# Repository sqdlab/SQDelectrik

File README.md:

# SQDelectrik

This repository details custom electronic circuits for general lab use. This repository holds the schematics and usage documentation:

- [Safe Ohmmeter](Projects/SafeOhmmeter/README.md)
- [Safe Ohmmeter v2](Projects/SafeOhmmeter2/README.md)

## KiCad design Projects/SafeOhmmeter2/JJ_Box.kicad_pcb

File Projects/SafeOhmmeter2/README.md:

# Safe Ohmmeter v2

Multimeters can measure resistance, but may set a large voltage across the device under test. Inspired by a [project in Delft](https://qtwork.tudelft.nl/~schouten/oldstuff/viboxjunction-p.htm), this is a modernised circuit that:

- Sets a fixed $10\textnormal{mV}$ across the sample
- Maps the resulting resistance into a voltage that is inversely proportional to the measured resistance
- This voltage can be read using a conventional multimeter set to voltage measurement mode

That is, this is a simple device aids in measuring resistance while keeping a safe voltage across the device under test.

## General usage

The device runs off 3 AA batteries:

The operation is as follows:

- The left dial turns on the device. When moving it midway between OFF and ON, it will light the LED to show that the battery is functional
- The toggle switch switches the polarity of the probe voltage across the device under test (measured from centre-pin to the ground-shield of the isolated BNC connector)
- The device under test is connected into the BNC connector labelled INPUT
- The resistance of the device under test is mapped onto a voltage from 1mV to 5V given by the range set by the right dial (selecting over: $1/R$, $100/R$ and $10000/R$). Measure this voltage via a multimeter connected to the OUTPUT BNC connector

There is a handy table that helps with the conversion between measured voltage and the sample resistance.

## Recalibrating the gains

The inputs should measure $\pm10\textnormal{mV}$. If not, then open the box and tune the VREF trimpot. Note that if it does not breach $10\textnormal{mV}$, check the batteries.

To recalibrate open the box and connect a resistor across the input and measure the voltage as follows:

- To tune the $1/R$ range, connect a $10\Omega$ resistor across the input and turn the $1/R$ trimpot so that the output reads exactly $0.1\textnormal{V}$.
- To tune the $100/R$ range, connect a $1\textnormal{k}\Omega$ resistor across the input and turn the $100/R$ trimpot so that the output reads exactly $0.1\textnormal{V}$.
- To tune the $10000/R$ range, connect a $100\textnormal{k}\Omega$ resistor across the input and turn the $10000/R$ trimpot so that the output reads exactly $0.1\textnormal{V}$.

The three trimpots on the PCB corresponding to the three ranges are:

## Method of operation

View the full schematic [here](Docs/Schematic.pdf). The device is a simple OPAMP amplifier:

- The OPAMP is fed a constant DC $10\textnormal{mV}$ on its $+$ input
- Since it is in negative feedback mode, the voltage on the $-$ input is also $10\textnormal{mV}$
- KCL at the $-$ input for a sample resistance $R_s$ and feedback resistance $R_f$ gives $V_-/R_S+(V_--V_{out})/R_f=0$
- This simplifies into: $V_{out}=R_f/R_sV_-+V_-$. Since the output is measured with respect to $V_+=V_-$, the stray $V_-$ disappears to give $V_{meas}=0.01R_f/R_s$
- The three ranges thus, take $R_f=100\Omega$, $R_f=10\textnormal{k}\Omega$ and $R_f=1\textnormal{M}\Omega$.

There are additional diodes to clamp the voltage as a protective measure. The voltage reference is also tuned to give $10\textnormal{mV}$ (although it can be compensated with the feedback trimpots as well).

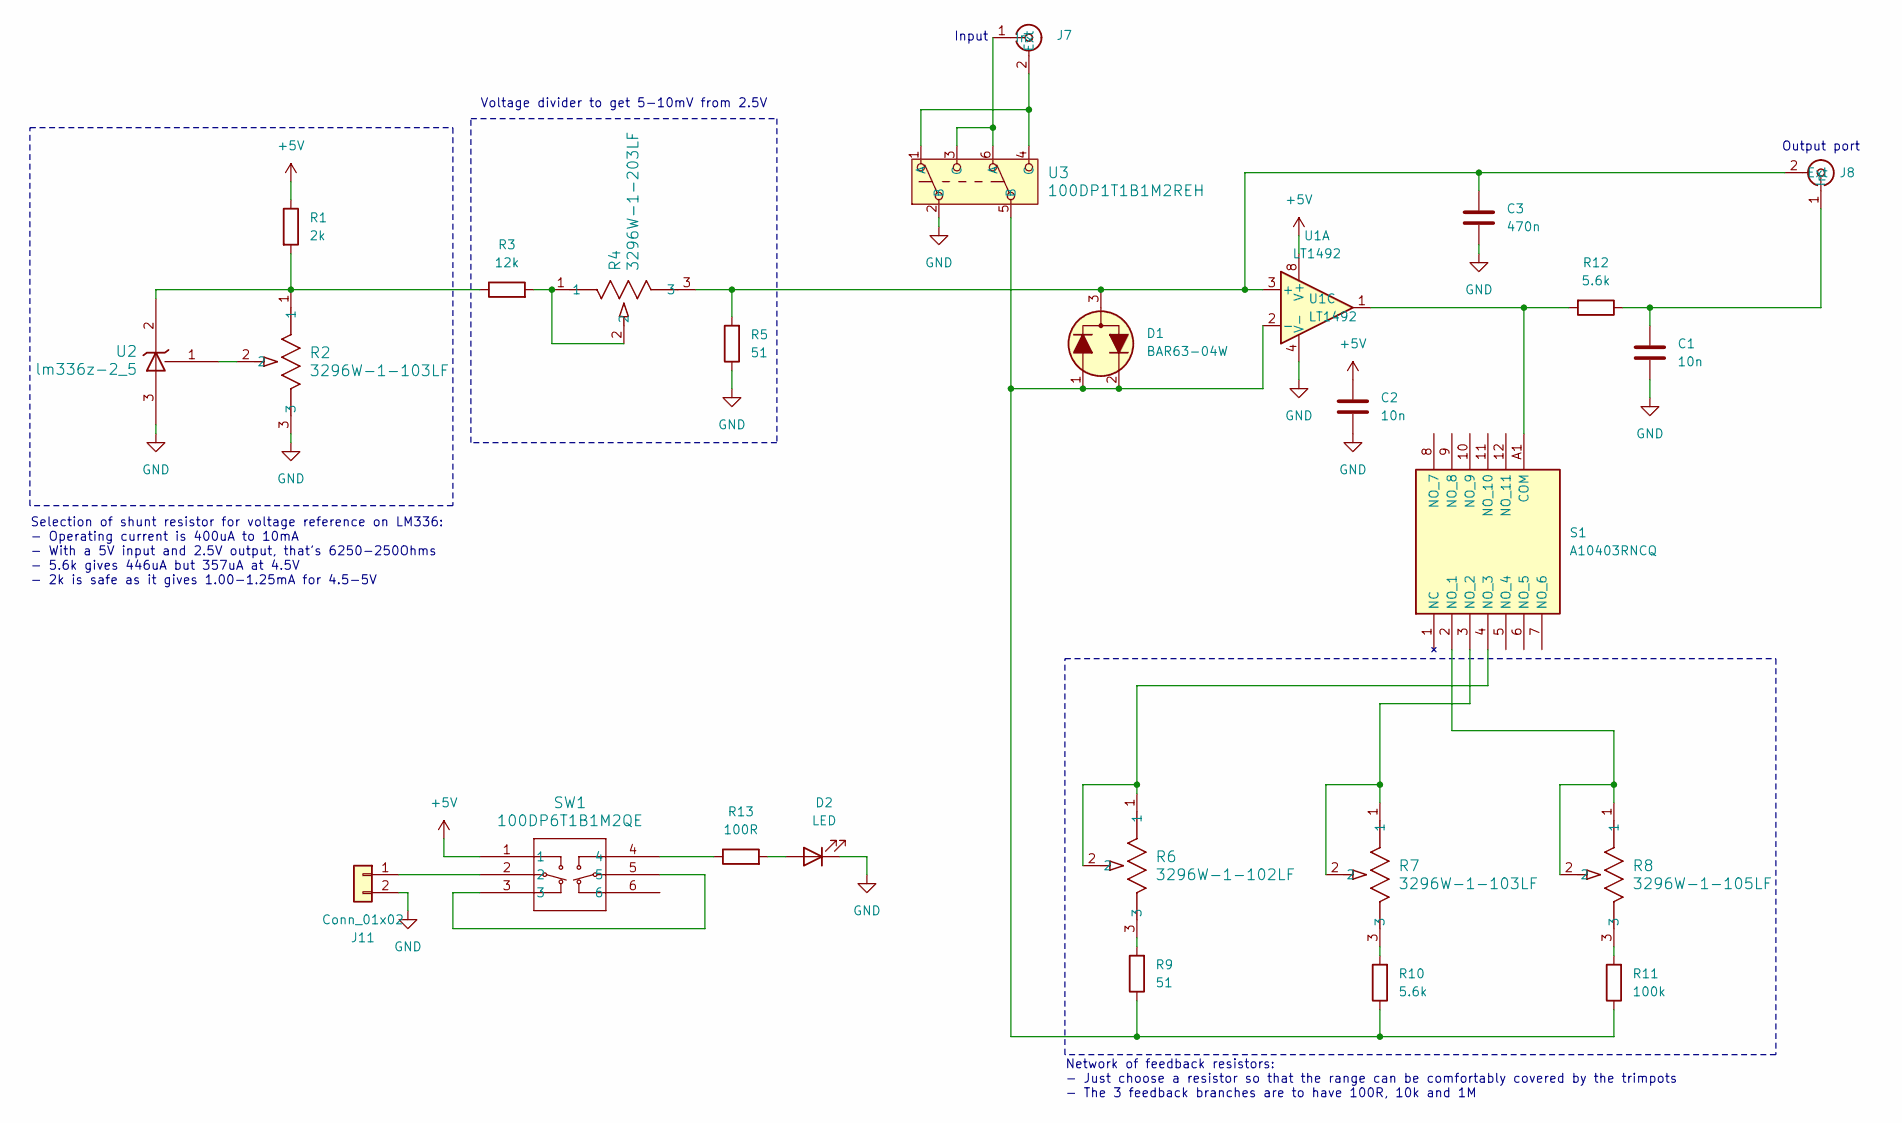
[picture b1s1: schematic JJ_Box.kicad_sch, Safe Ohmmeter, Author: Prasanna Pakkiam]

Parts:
C1, C2: 10n; C_0603_1608Metric_Pad1.08x0.95mm_HandSolder
C3: 470n; C_0603_1608Metric_Pad1.08x0.95mm_HandSolder
D1: BAR63-04W; SOT-323_SC-70_Handsoldering
D2: LED; LED_D5.0mm
J7, J8: CONN_5227222-3_TYC
J11: Conn_01x02; PinHeader_1x02_P2.54mm_Vertical
R1: 2k; R_0603_1608Metric_Pad0.98x0.95mm_HandSolder
R2, R7: 3296W-1-103LF; POT_3296W
R3: 12k; R_0603_1608Metric_Pad0.98x0.95mm_HandSolder
R4: 3296W-1-203LF; POT_3296W
R5, R9: 51; R_0603_1608Metric_Pad0.98x0.95mm_HandSolder
R6: 3296W-1-102LF; POT_3296W
R8: 3296W-1-105LF; POT_3296W
R10, R12: 5.6k; R_0603_1608Metric_Pad0.98x0.95mm_HandSolder
R11: 100k; R_0603_1608Metric_Pad0.98x0.95mm_HandSolder
R13: 100R; R_0603_1608Metric_Pad0.98x0.95mm_HandSolder
S1: A10403RNCQ; A10405RNCQE; Manufacturer_Part_Number A10403RNCQ
SW1: 100DP6T1B1M2QE; 100DP8T6B11M2QEH_EWI
U1: LT1492; SOIC-8_3.9x4.9mm_P1.27mm
U2: lm336z-2_5; Z03A_TEX
U3: 100DP1T1B1M2REH; SW6_100DP1T1B1M2REH

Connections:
+5V: C2.1, R1.1, SW1.1, U1.8 (V+)
GND: C1.2, C2.2, C3.2, D2.1 (K), J11.2, R2.3, R5.1, U1.4 (V-), U2.3 (-V), U3.2 (B)
unnamed: D1.1 (A), D1.2 (K), R9.1, R10.1, R11.1, U1.2 (-), U3.5 (B)
unnamed: C3.1, D1.3 (C), J8.2 (Ext), R4.3, R5.2, U1.3 (+)
unnamed: D2.2 (A), R13.2
unnamed: J7.2 (Ext), U3.1 (A), U3.4 (C)
unnamed: J7.1 (In), U3.3 (C), U3.6 (A)
unnamed: C1.1, J8.1 (In), R12.1
unnamed: J11.1, SW1.2
unnamed: R3.2, R4.1, R4.2
unnamed: R6.3, R9.2
unnamed: R7.3, R10.2
unnamed: R8.3, R11.2
unnamed: R13.1, SW1.4
unnamed: R12.2, S1.A1 (COM), U1.1
unnamed: R8.1, R8.2, S1.2 (NO_1)
unnamed: R7.1, R7.2, S1.3 (NO_2)
unnamed: R6.1, R6.2, S1.4 (NO_3)
unnamed: SW1.3, SW1.5
unnamed: R1.2, R2.1, R3.1, U2.2 (+V)
unnamed: R2.2, U2.1 (ADJ)

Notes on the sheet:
Voltage divider to get 5-10mV from 2.5V
Output port
Input
Network of feedback resistors: - Just choose a resistor so that the range can be comfortably covered by the trimpots - The 3 feedback branches are to have 100R, 10k and 1M
Selection of shunt resistor for voltage reference on LM336: - Operating current is 400uA to 10mA - With a 5V input and 2.5V output, that's 6250-250Ohms - 5.6k gives 446uA but 357uA at 4.5V - 2k is safe as it gives 1.00-1.25mA for 4.5-5V

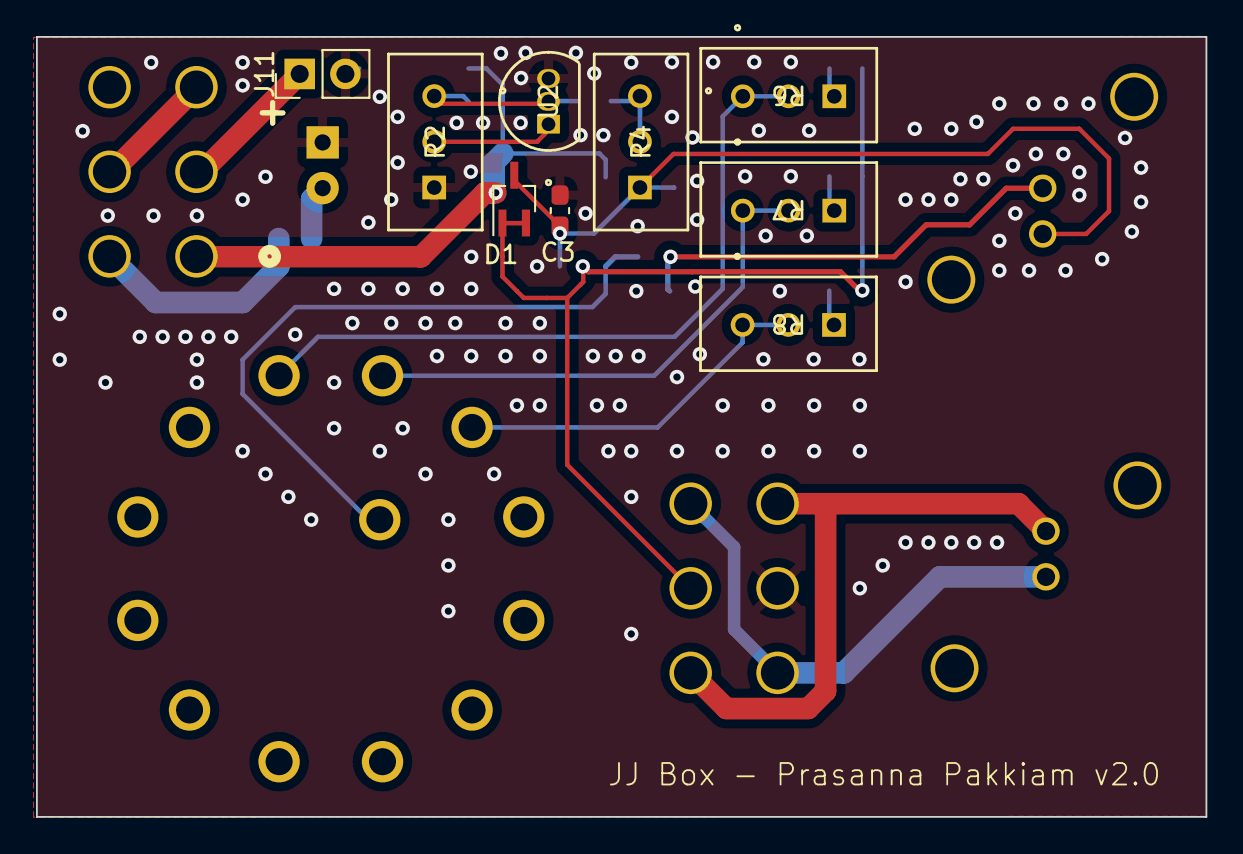
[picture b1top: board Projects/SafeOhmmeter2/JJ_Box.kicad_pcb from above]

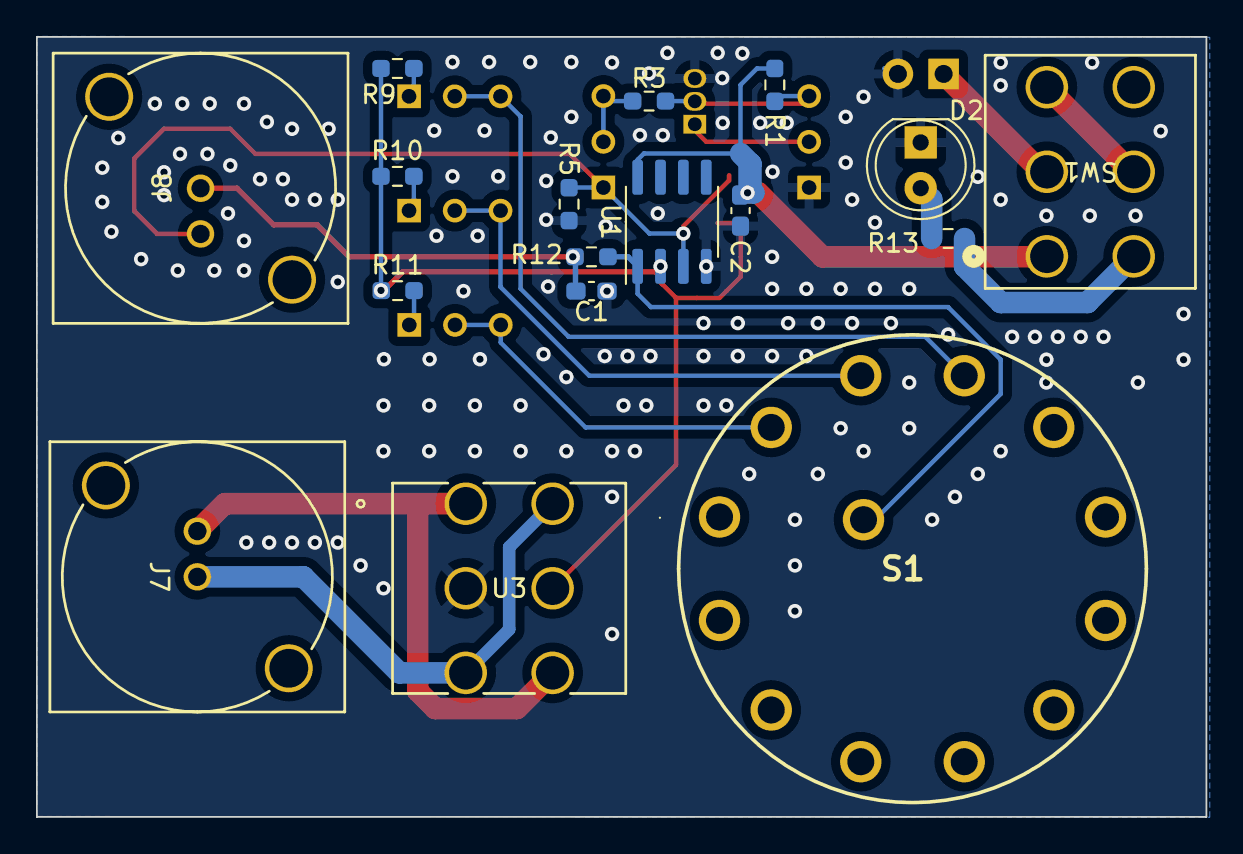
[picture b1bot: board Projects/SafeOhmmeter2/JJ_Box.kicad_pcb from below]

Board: 2 copper layers, 65.0 x 43.3 mm, 26 parts (17 on the bottom side), 21 nets.

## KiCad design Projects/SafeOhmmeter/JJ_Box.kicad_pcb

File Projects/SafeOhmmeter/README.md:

# Safe Ohmmeter

Multimeters can measure resistance, but may set a large voltage across the device under test. Inspired by a [project in Delft](https://qtwork.tudelft.nl/~schouten/oldstuff/viboxjunction-p.htm), this is a modernised circuit that:

- Sets a fixed $10\textnormal{mV}$ across the sample
- Maps the resulting resistance into a voltage that is inversely proportional to the measured resistance
- This voltage can be read using a conventional multimeter set to voltage measurement mode

That is, this is a simple device aids in measuring resistance while keeping a safe voltage across the device under test.

## General usage

The device runs off 3 AAA batteries:

The operation is as follows:

- The left dial turns on the device. When moving it midway between OFF and ON, it will light the LED to show that the battery is functional
- The toggle switch switches the polarity of the probe voltage across the device under test (measured from centre-pin to the ground-shield of the isolated BNC connector)
- The device under test is connected into the BNC connector labelled INPUT
- The resistance of the device under test is mapped onto a voltage from 1mV to 5V given by the range set by the right dial (selecting over: $1/R$, $100/R$ and $10000/R$). Measure this voltage via a multimeter connected to the OUTPUT BNC connector

There is a handy table that helps with the conversion between measured voltage and the sample resistance.

## Recalibrating the gains

To recalibrate open the box and connect a resistor across the input and measure the voltage as follows:

- To tune the $1/R$ range, connect a $10\Omega$ resistor across the input and turn the $1/R$ trimpot so that the output reads exactly $0.1\textnormal{V}$.
- To tune the $100/R$ range, connect a $1\textnormal{k}\Omega$ resistor across the input and turn the $100/R$ trimpot so that the output reads exactly $0.1\textnormal{V}$.
- To tune the $10000/R$ range, connect a $100\textnormal{k}\Omega$ resistor across the input and turn the $10000/R$ trimpot so that the output reads exactly $0.1\textnormal{V}$.

The three trimpots on the PCB corresponding to the three ranges are:

## Method of operation

View the full schematic [here](Docs/Schematic.pdf). The device is a simple OPAMP amplifier:

- The OPAMP is fed a constant DC $10\textnormal{mV}$ on its $+$ input
- Since it is in negative feedback mode, the voltage on the $-$ input is also $10\textnormal{mV}$
- KCL at the $-$ input for a sample resistance $R_s$ and feedback resistance $R_f$ gives $V_-/R_S+(V_--V_{out})/R_f=0$
- This simplifies into: $V_{out}=R_f/R_sV_-+V_-$. Since the output is measured with respect to $V_+=V_-$, the stray $V_-$ disappears to give $V_{meas}=0.01R_f/R_s$
- The three ranges thus, take $R_f=100\Omega$, $R_f=10\textnormal{k}\Omega$ and $R_f=1\textnormal{M}\Omega$.

There are additional diodes to clamp the voltage as a protective measure. The voltage reference is also tuned to give $10\textnormal{mV}$ (although it can be compensated with the feedback trimpots as well).

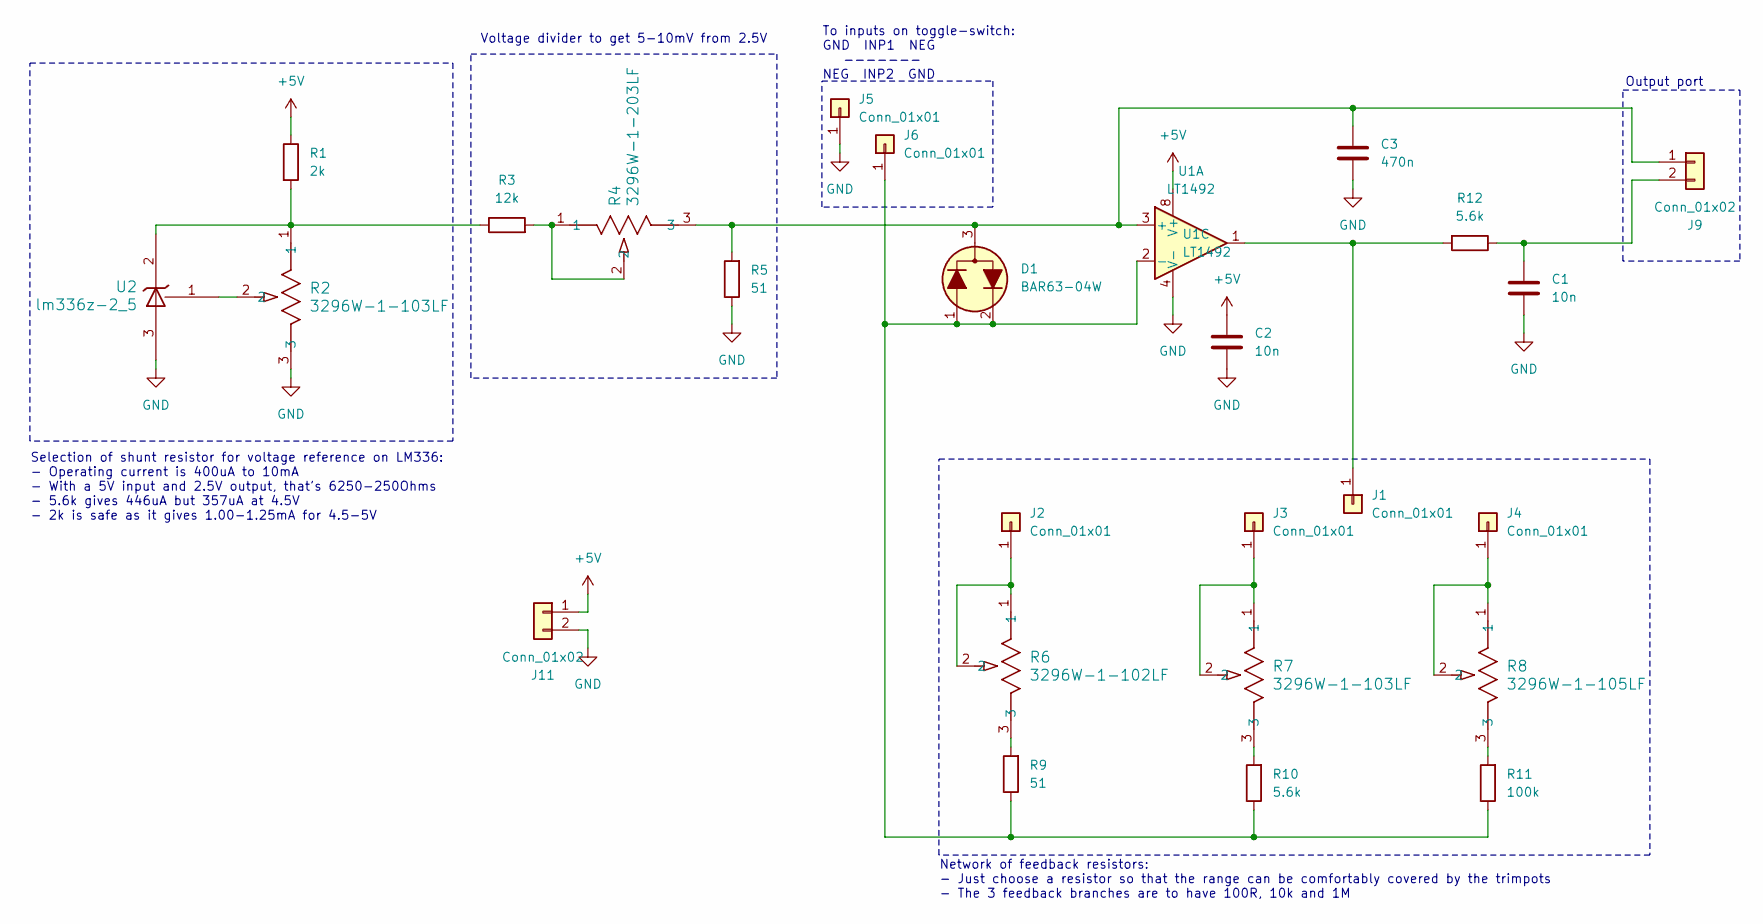
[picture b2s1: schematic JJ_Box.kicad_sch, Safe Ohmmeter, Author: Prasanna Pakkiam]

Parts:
C1, C2: 10n; C_0603_1608Metric_Pad1.08x0.95mm_HandSolder
C3: 470n; C_0603_1608Metric_Pad1.08x0.95mm_HandSolder
D1: BAR63-04W; SOT-323_SC-70_Handsoldering
J1, J2, J3, J4, J5, J6: Conn_01x01; PinHeader_1x01_P2.54mm_Vertical
J9, J11: Conn_01x02; PinHeader_1x02_P2.54mm_Vertical
R1: 2k; R_0603_1608Metric_Pad0.98x0.95mm_HandSolder
R2, R7: 3296W-1-103LF; POT_3296W
R3: 12k; R_0603_1608Metric_Pad0.98x0.95mm_HandSolder
R4: 3296W-1-203LF; POT_3296W
R5, R9: 51; R_0603_1608Metric_Pad0.98x0.95mm_HandSolder
R6: 3296W-1-102LF; POT_3296W
R8: 3296W-1-105LF; POT_3296W
R10, R12: 5.6k; R_0603_1608Metric_Pad0.98x0.95mm_HandSolder
R11: 100k; R_0603_1608Metric_Pad0.98x0.95mm_HandSolder
U1: LT1492; SOIC-8_3.9x4.9mm_P1.27mm
U2: lm336z-2_5; Z03A_TEX

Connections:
+5V: C2.1, J11.1, R1.1, U1.8 (V+)
GND: C1.2, C2.2, C3.2, J5.1, J11.2, R2.3, R5.1, U1.4 (V-), U2.3 (-V)
unnamed: D1.1 (A), D1.2 (K), J6.1, R9.1, R10.1, R11.1, U1.2 (-)
unnamed: C3.1, D1.3 (C), J9.1, R4.3, R5.2, U1.3 (+)
unnamed: J1.1, R12.2, U1.1
unnamed: J2.1, R6.1, R6.2
unnamed: J3.1, R7.1, R7.2
unnamed: J4.1, R8.1, R8.2
unnamed: C1.1, J9.2, R12.1
unnamed: R3.2, R4.1, R4.2
unnamed: R6.3, R9.2
unnamed: R7.3, R10.2
unnamed: R8.3, R11.2
unnamed: R1.2, R2.1, R3.1, U2.2 (+V)
unnamed: R2.2, U2.1 (ADJ)

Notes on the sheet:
Voltage divider to get 5-10mV from 2.5V
Output port
Network of feedback resistors: - Just choose a resistor so that the range can be comfortably covered by the trimpots - The 3 feedback branches are to have 100R, 10k and 1M
Selection of shunt resistor for voltage reference on LM336: - Operating current is 400uA to 10mA - With a 5V input and 2.5V output, that's 6250-250Ohms - 5.6k gives 446uA but 357uA at 4.5V - 2k is safe as it gives 1.00-1.25mA for 4.5-5V
To inputs on toggle-switch: GND INP1 NEG ------- NEG INP2 GND

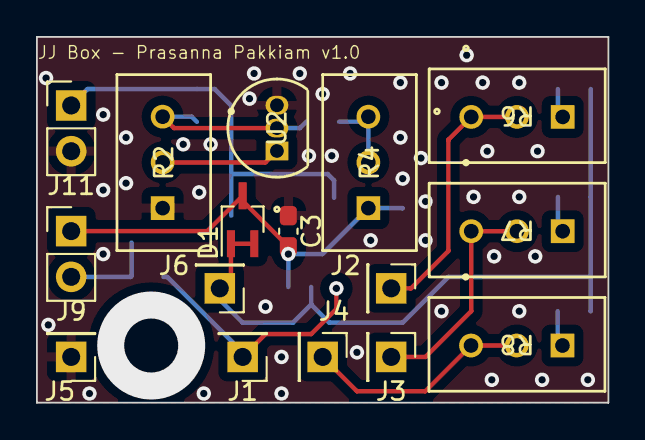
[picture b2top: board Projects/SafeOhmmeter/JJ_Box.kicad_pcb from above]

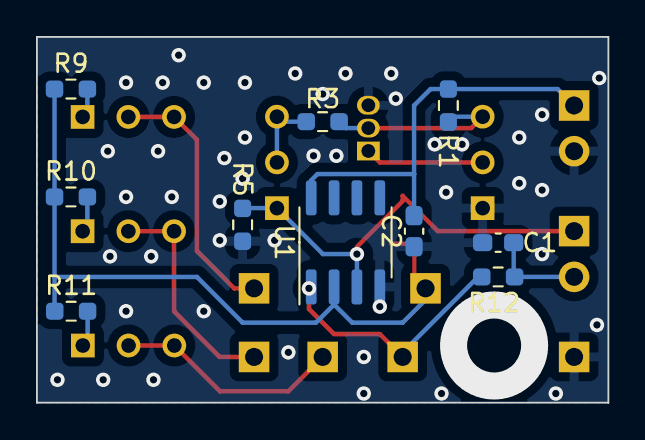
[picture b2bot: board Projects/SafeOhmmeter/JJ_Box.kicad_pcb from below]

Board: 2 copper layers, 31.8 x 20.3 mm, 26 parts (10 on the bottom side), 15 nets.

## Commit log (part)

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2024-10-18 Added safe-Ohmmeter.
